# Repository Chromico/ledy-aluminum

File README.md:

# Ledy Aluminum
An open source LED panel using Aluminum PCBs. This project was made in collaboration with https://pcbway.com .
My website: https://tecknologg.website

Blog post where I go into detail: https://link.tecknologg.website/k

# Schematic

# PCB

# Assembled board in action

# Contact

Need to contact me ? Just send me an email at nathan@tecknologg.website or tecknologg@gmail.com

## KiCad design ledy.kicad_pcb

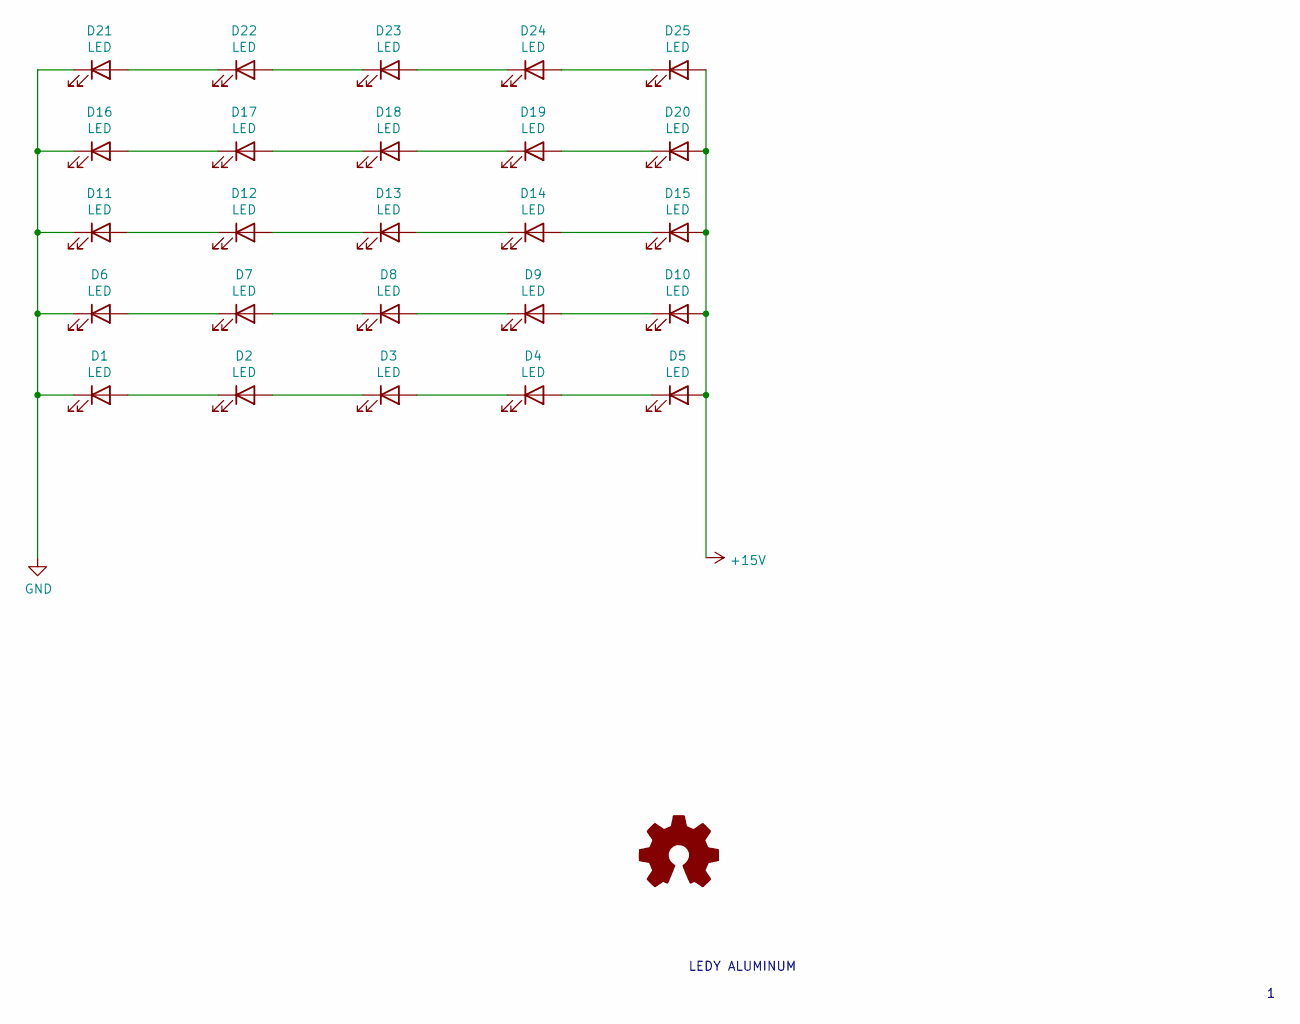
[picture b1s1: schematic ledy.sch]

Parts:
D1, D2, D3, D4, D5, D6, D7, D8, D9, D10, D11, D12, D13, D14, D15, D16, D17, D18, D19, D20, D21, D22, D23, D24, D25: LED

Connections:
+15V: D5.2 (A), D10.2 (A), D15.2 (A), D20.2 (A), D25.2 (A); also elsewhere on the board
GND: D1.1 (K), D6.1 (K), D11.1 (K), D16.1 (K), D21.1 (K); also elsewhere on the board
unnamed: D1.2 (A), D2.1 (K)
unnamed: D2.2 (A), D3.1 (K)
unnamed: D3.2 (A), D4.1 (K)
unnamed: D4.2 (A), D5.1 (K)
unnamed: D6.2 (A), D7.1 (K)
unnamed: D7.2 (A), D8.1 (K)
unnamed: D8.2 (A), D9.1 (K)
unnamed: D9.2 (A), D10.1 (K)
unnamed: D11.2 (A), D12.1 (K)
unnamed: D12.2 (A), D13.1 (K)
unnamed: D13.2 (A), D14.1 (K)
unnamed: D14.2 (A), D15.1 (K)
unnamed: D16.2 (A), D17.1 (K)
unnamed: D17.2 (A), D18.1 (K)
unnamed: D18.2 (A), D19.1 (K)
unnamed: D19.2 (A), D20.1 (K)
unnamed: D21.2 (A), D22.1 (K)
unnamed: D22.2 (A), D23.1 (K)
unnamed: D23.2 (A), D24.1 (K)
unnamed: D24.2 (A), D25.1 (K)

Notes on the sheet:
LEDY ALUMINUM

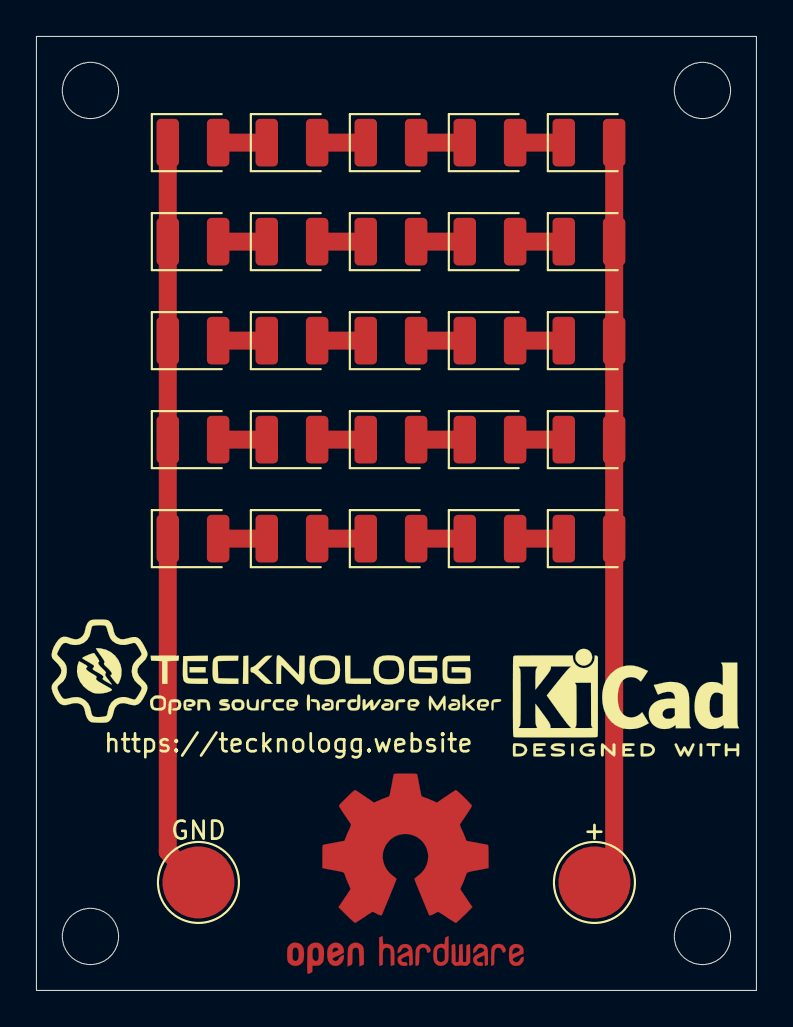
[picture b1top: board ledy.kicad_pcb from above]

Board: 2 copper layers, 40.0 x 53.0 mm, 27 parts (0 on the bottom side), 22 nets.

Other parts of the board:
+: TestPoint_Pad_D4.0mm
GND: TestPoint_Pad_D4.0mm

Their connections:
+15V: +.1; also elsewhere on the board
GND: GND.1; also elsewhere on the board

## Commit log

2020-11-30 [ImgBot] Optimize images
    *Total -- 3,365.27kb -> 3,176.41kb (5.61%)
    /pics/ledy-aluminum-pcb.png -- 34.13kb -> 27.04kb (20.75%)
    /pics/ledy-aluminum-schematic-700x524.png -- 43.64kb -> 37.85kb (13.26%)
    /pics/20201124_003739.jpg -- 3,287.51kb -> 3,111.51kb (5.35%)
2020-11-30 Update LICENSE
